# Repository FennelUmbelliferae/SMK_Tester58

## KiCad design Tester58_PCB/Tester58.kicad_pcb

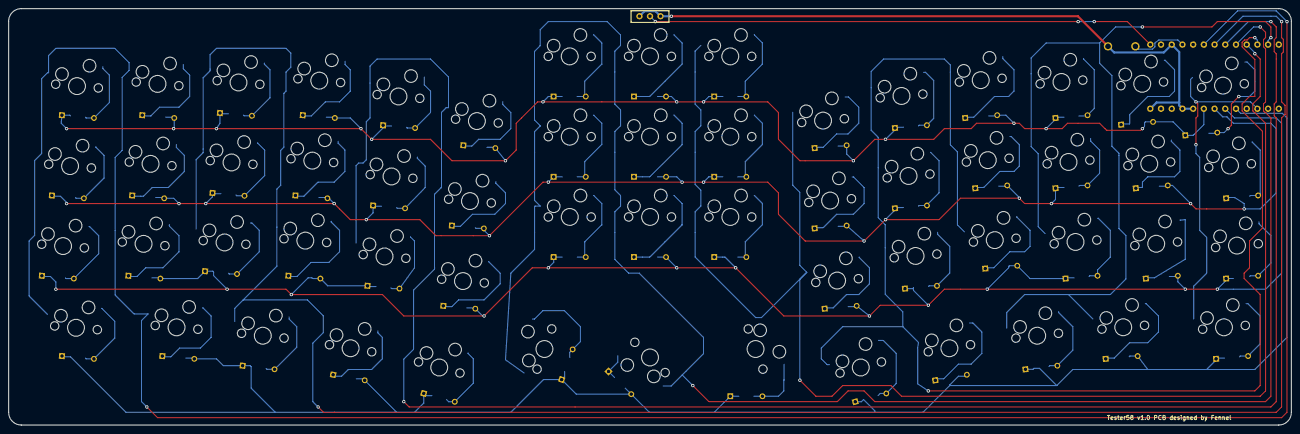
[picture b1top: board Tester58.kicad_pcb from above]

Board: 2 copper layers, 304.4 x 98.8 mm, 119 parts (0 on the bottom side), 73 nets.

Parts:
D1, D2, D3, D4, D5, D6, D7, D8, D9, D10, D11, D12, D13, D14, D15, D16, D17, D18, D19, D20, D21, D22, D23, D24, D25, D26, D27, D28, D29, D30, D31, D32, D33, D34, D35, D36, D37, D38, D39, D40, D41, D42, D43, D44, D45, D46, D47, D48, D49, D50, D51, D52, D53, D54, D55, D56, D57, D58: D; Diode_TH_SMD
J1: Conn_01x02; Battery_XH2.5_GL_PCB
SW1, SW2, SW3, SW5, SW6, SW7, SW8, SW9, SW10, SW11, SW12, SW13, SW14, SW15, SW17, SW18, SW19, SW21, SW22, SW23, SW24, SW25, SW26, SW27, SW28, SW30, SW31, SW33, SW34, SW35, SW36, SW37, SW38, SW39, SW40, SW41, SW42, SW43, SW44, SW45, SW46, SW47, SW48, SW49, SW50, SW51, SW52, SW53, SW54, SW56, SW57, SW58: SW_PUSH; CherryMX_Hotswap_1u
SW4, SW16, SW20, SW32: SW_PUSH; CherryMX_Hotswap_1.5u
SW29, SW55: SW_PUSH; CherryMX_Hotswap_1u_Small1
SW59: SW_PUSH; ResetSW
U1: BLEMicroPro; Micon_BMP_GL

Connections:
Bat+: J1.1, U1.25
Col0: SW1.1, SW2.1, SW3.1, SW4.1, SW33.1, SW34.1, SW35.1, SW36.1, U1.20
Col1: SW5.1, SW6.1, SW7.1, SW8.1, SW37.1, SW38.1, SW39.1, SW40.1, U1.19
Col2: SW9.1, SW10.1, SW11.1, SW12.1, SW41.1, SW42.1, SW43.1, U1.18
Col3: SW13.1, SW14.1, SW15.1, SW16.1, SW44.1, SW45.1, SW46.1, SW47.1, U1.17
Col4: SW17.1, SW18.1, SW19.1, SW20.1, SW48.1, SW49.1, SW50.1, U1.16
Col5: SW21.1, SW22.1, SW23.1, SW24.1, SW51.1, SW52.1, SW53.1, SW54.1, U1.15
Col6: SW25.1, SW26.1, SW27.1, SW28.1, SW55.1, SW56.1, SW57.1, SW58.1, U1.14
Col7: SW29.1, SW30.1, SW31.1, SW32.1, U1.10
GND: J1.2, SW59.2, U1.3, U1.4, U1.23, U1.26
unnamed: D1.2, SW1.2
unnamed: D2.2, SW2.2
unnamed: D3.2, SW3.2
unnamed: D4.2, SW4.2
unnamed: D5.2, SW5.2
unnamed: D6.2, SW6.2
unnamed: D7.2, SW7.2
unnamed: D8.2, SW8.2
unnamed: D9.2, SW9.2
unnamed: D10.2, SW10.2
unnamed: D11.2, SW11.2
unnamed: D12.2, SW12.2
unnamed: D13.2, SW13.2
unnamed: D14.2, SW14.2
unnamed: D15.2, SW15.2
unnamed: D16.2, SW16.2
unnamed: D17.2, SW17.2
unnamed: D18.2, SW18.2
unnamed: D19.2, SW19.2
unnamed: D20.2, SW20.2
unnamed: D21.2, SW21.2
unnamed: D22.2, SW22.2
unnamed: D23.2, SW23.2
unnamed: D24.2, SW24.2
unnamed: D25.2, SW25.2
unnamed: D26.2, SW26.2
unnamed: D27.2, SW27.2
unnamed: D28.2, SW28.2
unnamed: D29.2, SW29.2
unnamed: D30.2, SW30.2
unnamed: D31.2, SW31.2
unnamed: D32.2, SW32.2
unnamed: D33.1, SW33.2
unnamed: D34.1, SW34.2
unnamed: D35.1, SW35.2
unnamed: D36.1, SW36.2
unnamed: D37.1, SW37.2
unnamed: D38.1, SW38.2
unnamed: D39.1, SW39.2
unnamed: D40.1, SW40.2
unnamed: D41.1, SW41.2
unnamed: D42.1, SW42.2
unnamed: D43.1, SW43.2
unnamed: D44.1, SW44.2
unnamed: D45.1, SW45.2
unnamed: D46.1, SW46.2
unnamed: D47.1, SW47.2
unnamed: D48.1, SW48.2
unnamed: D49.1, SW49.2
unnamed: D50.1, SW50.2
unnamed: D51.1, SW51.2
unnamed: D52.1, SW52.2
unnamed: D53.1, SW53.2
unnamed: D54.1, SW54.2
unnamed: D55.1, SW55.2
unnamed: D56.1, SW56.2
unnamed: D57.1, SW57.2
unnamed: D58.1, SW58.2
Reset: SW59.1, U1.22
Row0: D1.1, D5.1, D9.1, D13.1, D17.1, D21.1, D25.1, D29.1, D33.2, D37.2, D41.2, D44.2, D48.2, D51.2, D55.2, U1.5
Row1: D2.1, D6.1, D10.1, D14.1, D18.1, D22.1, D26.1, D30.1, D34.2, D38.2, D42.2, D45.2, D49.2, D52.2, D56.2, U1.6
Row2: D3.1, D7.1, D11.1, D15.1, D19.1, D23.1, D27.1, D31.1, D35.2, D39.2, D43.2, D46.2, D50.2, D53.2, D57.2, U1.7
Row3: D4.1, D8.1, D12.1, D16.1, D20.1, D24.1, D28.1, D32.1, D36.2, D40.2, D47.2, D54.2, D58.2, U1.8

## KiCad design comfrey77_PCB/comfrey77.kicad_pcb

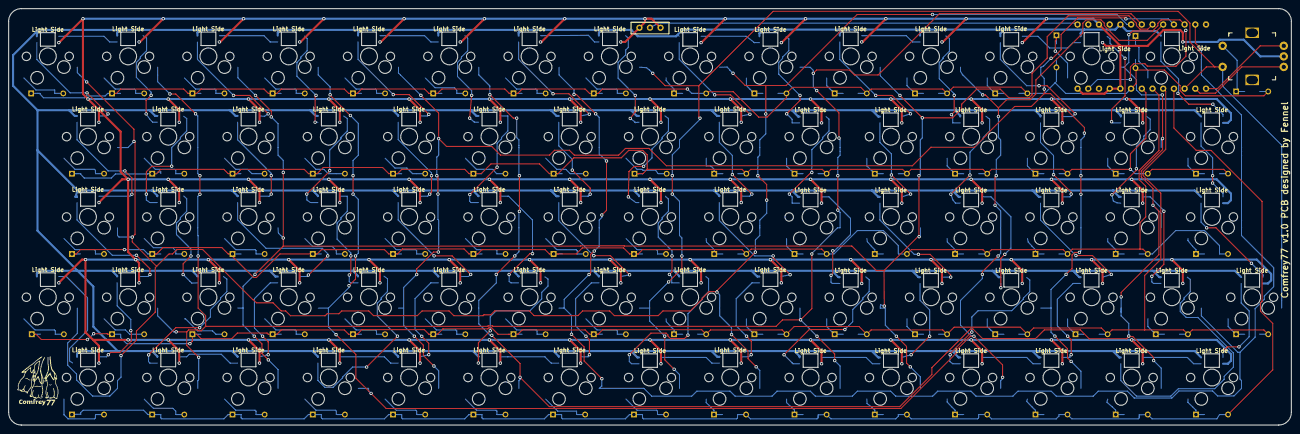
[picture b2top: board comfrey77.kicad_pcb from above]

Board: 2 copper layers, 304.4 x 98.8 mm, 232 parts (0 on the bottom side), 171 nets.

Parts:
D1, D2, D3, D4, D5, D6, D7, D8, D9, D10, D11, D12, D13, D14, D15, D16, D17, D18, D19, D20, D21, D22, D23, D24, D25, D26, D27, D28, D29, D30, D31, D32, D33, D34, D35, D36, D37, D38, D39, D40, D41, D42, D43, D44, D45, D46, D47, D48, D49, D50, D51, D52, D53, D54, D55, D56, D57, D58, D59, D60, D61, D62, D63, D64, D65, D66, D67, D68, D69, D70, D71, D72, D73, D74, D75, D76, D77: D; Diode_TH_SMD
J1: Conn_01x02; Battery_XH2.5_GL_PCB
L1, L2, L3, L4, L5, L6, L7, L8, L9, L10, L11, L12, L13, L14, L15, L16, L17, L18, L19, L20, L21, L22, L23, L24, L25, L26, L27, L28, L29, L30, L31, L32, L33, L34, L35, L36, L37, L38, L39, L40, L41, L42, L43, L44, L45, L46, L47, L48, L49, L50, L51, L52, L53, L54, L55, L56, L57, L58, L59, L60, L61, L62, L63, L64, L65, L66, L67, L68, L69, L70, L71, L72, L73, L74, L75, L76: SK6812MINI; LED_SK6812MINI-E_BL
SW1, SW2, SW3, SW4, SW5, SW6, SW7, SW8, SW9, SW10, SW11, SW12, SW13, SW14, SW15, SW16, SW17, SW18, SW19, SW20, SW21, SW22, SW23, SW24, SW25, SW26, SW27, SW28, SW29, SW30, SW31, SW32, SW33, SW34, SW35, SW36, SW37, SW38, SW39, SW40, SW41, SW42, SW43, SW44, SW45, SW46, SW47, SW48, SW49, SW50, SW51, SW52, SW53, SW54, SW55, SW56, SW57, SW58, SW59, SW60, SW61, SW62, SW63, SW64, SW65, SW66, SW67, SW68, SW69, SW70, SW71, SW72, SW73, SW74, SW75, SW77: SW_PUSH; CherryMX_Hotswap_1u
SW76: Rotary_Encoder_Switch; RotaryEncoder_EC12E
U1: BLEMicroPro; Micon_BMP_GL

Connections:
A1: SW76.A, U1.11
B1: SW76.B, U1.12
Bat+: J1.1, U1.25
Col0: SW1.1, SW2.1, SW3.1, SW4.1, SW5.1, SW41.1, SW42.1, SW43.1, SW44.1, SW45.1, U1.20
Col1: SW6.1, SW7.1, SW8.1, SW9.1, SW10.1, SW46.1, SW47.1, SW48.1, SW49.1, SW50.1, U1.19
Col2: SW11.1, SW12.1, SW13.1, SW14.1, SW15.1, SW51.1, SW52.1, SW53.1, SW54.1, SW55.1, U1.18
Col3: SW16.1, SW17.1, SW18.1, SW19.1, SW20.1, SW56.1, SW57.1, SW58.1, SW59.1, SW60.1, U1.17
Col4: SW21.1, SW22.1, SW23.1, SW24.1, SW25.1, SW61.1, SW62.1, SW63.1, SW64.1, SW65.1, U1.16
Col5: SW26.1, SW27.1, SW28.1, SW29.1, SW30.1, SW66.1, SW67.1, SW68.1, SW69.1, SW70.1, U1.15
Col6: SW31.1, SW32.1, SW33.1, SW34.1, SW35.1, SW71.1, SW72.1, SW73.1, SW74.1, SW75.1, U1.14
Col7: SW36.1, SW37.1, SW38.1, SW39.1, SW40.1, SW76.S2, SW77.1, U1.10
GND: J1.2, L1.2, L2.2, L3.2, L4.2, L5.2, L6.2, L7.2, L8.2, L9.2, L10.2, L11.2, L12.2, L13.2, L14.2, L15.2, L16.2, L17.2, L18.2, L19.2, L20.2, L21.2, L22.2, L23.2, L24.2, L25.2, L26.2, L27.2, L28.2, L29.2, L30.2, L31.2, L32.2, L33.2, L34.2, L35.2, L36.2, L37.2, L38.2, L39.2, L40.2, L41.2, L42.2, L43.2, L44.2, L45.2, L46.2, L47.2, L48.2, L49.2, L50.2, L51.2, L52.2, L53.2, L54.2, L55.2, L56.2, L57.2, L58.2, L59.2, L60.2, L61.2, L62.2, L63.2, L64.2, L65.2, L66.2, L67.2, L68.2, L69.2, L70.2, L71.2, L72.2, L73.2, L74.2, L75.2, L76.2, SW76.C, U1.3, U1.4, U1.23, U1.26
LED: L1.3, U1.1
unnamed: D1.2, SW1.2
unnamed: D2.2, SW2.2
unnamed: D3.2, SW3.2
unnamed: D4.2, SW4.2
unnamed: D5.2, SW5.2
unnamed: D6.2, SW6.2
unnamed: D7.2, SW7.2
unnamed: D8.2, SW8.2
unnamed: D9.2, SW9.2
unnamed: D10.2, SW10.2
unnamed: D11.2, SW11.2
unnamed: D12.2, SW12.2
unnamed: D13.2, SW13.2
unnamed: D14.2, SW14.2
unnamed: D15.2, SW15.2
unnamed: D16.2, SW16.2
unnamed: D17.2, SW17.2
unnamed: D18.2, SW18.2
unnamed: D19.2, SW19.2
unnamed: D20.2, SW20.2
unnamed: D21.2, SW21.2
unnamed: D22.2, SW22.2
unnamed: D23.2, SW23.2
unnamed: D24.2, SW24.2
unnamed: D25.2, SW25.2
unnamed: D26.2, SW26.2
unnamed: D27.2, SW27.2
unnamed: D28.2, SW28.2
unnamed: D29.2, SW29.2
unnamed: D30.2, SW30.2
unnamed: D31.2, SW31.2
unnamed: D32.2, SW32.2
unnamed: D33.2, SW33.2
unnamed: D34.2, SW34.2
unnamed: D35.2, SW35.2
unnamed: D36.2, SW36.2
unnamed: D37.2, SW37.2
unnamed: D38.2, SW38.2
unnamed: D39.2, SW39.2
unnamed: D40.2, SW40.2
unnamed: D41.1, SW41.2
unnamed: D42.1, SW42.2
unnamed: D43.1, SW43.2
unnamed: D44.1, SW44.2
unnamed: D45.1, SW45.2
unnamed: D46.1, SW46.2
unnamed: D47.1, SW47.2
unnamed: D48.1, SW48.2
unnamed: D49.1, SW49.2
unnamed: D50.1, SW50.2
unnamed: D51.1, SW51.2
unnamed: D52.1, SW52.2
unnamed: D53.1, SW53.2
unnamed: D54.1, SW54.2
unnamed: D55.1, SW55.2
unnamed: D56.1, SW56.2
unnamed: D57.1, SW57.2
unnamed: D58.1, SW58.2
unnamed: D59.1, SW59.2
unnamed: D60.1, SW60.2
unnamed: D61.1, SW61.2
unnamed: D62.1, SW62.2
unnamed: D63.1, SW63.2
unnamed: D64.1, SW64.2
unnamed: D65.1, SW65.2
unnamed: D66.1, SW66.2
unnamed: D67.1, SW67.2
unnamed: D68.1, SW68.2
unnamed: D69.1, SW69.2
unnamed: D70.1, SW70.2
unnamed: D71.1, SW71.2
unnamed: D72.1, SW72.2
unnamed: D73.1, SW73.2
unnamed: D74.1, SW74.2
unnamed: D75.1, SW75.2
unnamed: D76.1, SW76.S1
unnamed: D77.1, SW77.2
unnamed: L1.1, L2.3
unnamed: L2.1, L3.3
unnamed: L3.1, L4.3
unnamed: L4.1, L5.3
unnamed: L5.1, L6.3
unnamed: L6.1, L7.3
unnamed: L7.1, L8.3
unnamed: L8.1, L9.3
unnamed: L10.1, L11.3
unnamed: L9.1, L10.3
unnamed: L11.1, L12.3
unnamed: L12.1, L13.3
unnamed: L13.1, L14.3
unnamed: L14.1, L15.3
unnamed: L15.1, L16.3
unnamed: L16.1, L17.3
unnamed: L17.1, L18.3
unnamed: L18.1, L19.3
unnamed: L19.1, L20.3
unnamed: L20.1, L21.3
unnamed: L21.1, L22.3
unnamed: L22.1, L23.3
unnamed: L23.1, L24.3
unnamed: L24.1, L25.3
unnamed: L25.1, L26.3
unnamed: L26.1, L27.3
unnamed: L27.1, L28.3
unnamed: L28.1, L29.3
unnamed: L29.1, L30.3
unnamed: L30.1, L31.3
unnamed: L31.1, L32.3
unnamed: L32.1, L33.3
unnamed: L33.1, L34.3
unnamed: L34.1, L35.3
unnamed: L35.1, L36.3
unnamed: L36.1, L37.3
unnamed: L37.1, L38.3
unnamed: L38.1, L39.3
unnamed: L39.1, L40.3
unnamed: L40.1, L41.3
unnamed: L41.1, L42.3
unnamed: L42.1, L43.3
unnamed: L43.1, L44.3
unnamed: L44.1, L45.3
unnamed: L45.1, L46.3
unnamed: L46.1, L47.3
unnamed: L47.1, L48.3
unnamed: L48.1, L49.3
unnamed: L49.1, L50.3
unnamed: L50.1, L51.3
unnamed: L51.1, L52.3
unnamed: L52.1, L53.3
unnamed: L53.1, L54.3
unnamed: L54.1, L55.3
unnamed: L55.1, L56.3
unnamed: L56.1, L57.3
unnamed: L57.1, L58.3
unnamed: L58.1, L59.3
unnamed: L59.1, L60.3
unnamed: L60.1, L61.3
unnamed: L61.1, L62.3
unnamed: L62.1, L63.3
unnamed: L63.1, L64.3
unnamed: L64.1, L65.3
unnamed: L65.1, L66.3
unnamed: L66.1, L67.3
unnamed: L67.1, L68.3
unnamed: L68.1, L69.3
unnamed: L69.1, L70.3
unnamed: L70.1, L71.3
unnamed: L71.1, L72.3
unnamed: L72.1, L73.3
unnamed: L73.1, L74.3
unnamed: L74.1, L75.3
unnamed: L75.1, L76.3
Row0: D1.1, D6.1, D11.1, D16.1, D21.1, D26.1, D31.1, D36.1, D41.2, D46.2, D51.2, D56.2, D61.2, D66.2, D71.2, D76.2, U1.5
Row1: D2.1, D7.1, D12.1, D17.1, D22.1, D27.1, D32.1, D37.1, D42.2, D47.2, D52.2, D57.2, D62.2, D67.2, D72.2, U1.6
Row2: D3.1, D8.1, D13.1, D18.1, D23.1, D28.1, D33.1, D38.1, D43.2, D48.2, D53.2, D58.2, D63.2, D68.2, D73.2, U1.7
Row3: D4.1, D9.1, D14.1, D19.1, D24.1, D29.1, D34.1, D39.1, D44.2, D49.2, D54.2, D59.2, D64.2, D69.2, D74.2, D77.2, U1.8
Row4: D5.1, D10.1, D15.1, D20.1, D25.1, D30.1, D35.1, D40.1, D45.2, D50.2, D55.2, D60.2, D65.2, D70.2, D75.2, U1.9
VCC: L1.4, L2.4, L3.4, L4.4, L5.4, L6.4, L7.4, L8.4, L9.4, L10.4, L11.4, L12.4, L13.4, L14.4, L15.4, L16.4, L17.4, L18.4, L19.4, L20.4, L21.4, L22.4, L23.4, L24.4, L25.4, L26.4, L27.4, L28.4, L29.4, L30.4, L31.4, L32.4, L33.4, L34.4, L35.4, L36.4, L37.4, L38.4, L39.4, L40.4, L41.4, L42.4, L43.4, L44.4, L45.4, L46.4, L47.4, L48.4, L49.4, L50.4, L51.4, L52.4, L53.4, L54.4, L55.4, L56.4, L57.4, L58.4, L59.4, L60.4, L61.4, L62.4, L63.4, L64.4, L65.4, L66.4, L67.4, L68.4, L69.4, L70.4, L71.4, L72.4, L73.4, L74.4, L75.4, L76.4, U1.21

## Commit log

2022-01-26 Tester58
2022-03-20 add LOGO
2022-03-25 Create LICENSE
